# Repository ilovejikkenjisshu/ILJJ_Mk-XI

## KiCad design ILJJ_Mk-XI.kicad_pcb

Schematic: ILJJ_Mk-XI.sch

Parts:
D0: LED; LED_D5.0mm
D1, D2, D3, D4, D5, D6, D7, D8, D9, D10, D11, D12, D13, D14, D15, D16, D17, D18, D19, D20, D21, D22, D23, D24: LED; LED_Rectangular_W5.0mm_H2.0mm
J0, J1, J2, J3: Conn_02x12_Odd_Even; 5530843-1_socket
J4: Conn_02x12_Odd_Even; Pin_Header_Straight_2x12_Pitch2.54mm
J5: Conn_02x12_Odd_Even; Socket_Strip_Straight_2x12_Pitch2.54mm
R0, R1, R2, R3, R4, R5, R6, R7, R8, R9, R10, R11, R12, R13, R14, R15, R16, R17, R18, R19, R20, R21, R22, R23, R24, R25, R26, R27, R28, R29, R30, R31, R32, R33, R34, R35, R36, R37, R38, R39, R40: R; R_Axial_DIN0204_L3.6mm_D1.6mm_P2.54mm_Vertical
SW0, SW1, SW2, SW3: SW_Coded_SH-7070; Nidec_Copal_SH-7010C
U1, U2, U3: 7400; DIP-14_W7.62mm_LongPads

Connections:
/A0: J0.23, R0.1, R32.1, SW0.1
/A1: J0.21, R1.1, R31.1, SW0.2
/A2: J1.23, R2.1, R30.1, SW0.4
/A3: J1.21, R3.1, R29.1, SW0.8
/A4: J2.23, R4.1, R28.1, SW1.1
/A5: J2.21, R5.1, R27.1, SW1.2
/A6: J3.23, R6.1, R26.1, SW1.4
/A7: J3.21, R7.1, R25.1, SW1.8
/B0: J0.24, R8.1, R40.1, SW2.1
/B1: J0.22, R9.1, R39.1, SW2.2
/B2: J1.24, R10.1, R38.1, SW2.4
/B3: J1.22, R11.1, R37.1, SW2.8
/B4: J2.24, R12.1, R36.1, SW3.1
/B5: J2.22, R13.1, R35.1, SW3.2
/B6: J3.24, R14.1, R34.1, SW3.4
/B7: J3.22, R15.1, R33.1, SW3.8
/F0: J4.7, J4.8, J5.7, J5.8, U3.1, U3.2, U3.4, U3.5
/F0_1: J0.7, J0.8, J1.7, J1.8, U3.11
/F0_2: J2.7, J2.8, J3.7, J3.8, U3.8
/F1: J4.5, J4.6, J5.5, J5.6, U2.1, U2.2, U2.4, U2.5
/F1_1: J0.5, J0.6, J1.5, J1.6, U2.11
/F1_2: J2.5, J2.6, J3.5, J3.6, U2.8
/F2: J4.3, J4.4, J5.3, J5.4, U1.1, U1.2, U1.4, U1.5
/F2_1: J0.3, J0.4, J1.3, J1.4, U1.11
/F2_2: J2.3, J2.4, J3.3, J3.4, U1.8
/S0: J0.16, R24.1
/S1: J0.14, R23.1
/S2: J1.16, R22.1
/S3: J1.14, R21.1
/S4: J2.16, R20.1
/S5: J2.14, R19.1
/S6: J3.16, R18.1
/S7: J3.14, R17.1
unnamed: D0.2, R16.2
unnamed: D1.2, R17.2
unnamed: D2.2, R18.2
unnamed: D3.2, R19.2
unnamed: D4.2, R20.2
unnamed: D5.2, R21.2
unnamed: D6.2, R22.2
unnamed: D7.2, R23.2
unnamed: D8.2, R24.2
unnamed: D9.2, R25.2
unnamed: D10.2, R26.2
unnamed: D11.2, R27.2
unnamed: D12.2, R28.2
unnamed: D13.2, R29.2
unnamed: D14.2, R30.2
unnamed: D15.2, R31.2
unnamed: D16.2, R32.2
unnamed: D17.2, R33.2
unnamed: D18.2, R34.2
unnamed: D19.2, R35.2
unnamed: D20.2, R36.2
unnamed: D21.2, R37.2
unnamed: D22.2, R38.2
unnamed: D23.2, R39.2
unnamed: D24.2, R40.2
unnamed: J0.9, J4.19, J4.20
unnamed: J0.10, J1.9
unnamed: J1.10, J2.9
unnamed: J2.10, J3.9
unnamed: J3.10, J5.19, J5.20
unnamed: U1.6, U1.9, U1.10
unnamed: U1.3, U1.12, U1.13
unnamed: U2.6, U2.9, U2.10
unnamed: U2.3, U2.12, U2.13
unnamed: U3.6, U3.9, U3.10
unnamed: U3.3, U3.12, U3.13
VCC: J0.1, J0.2, J1.1, J1.2, J2.1, J2.2, J3.1, J3.2, J4.1, J4.2, J5.1, J5.2, R0.2, R1.2, R2.2, R3.2, R4.2, R5.2, R6.2, R7.2, R8.2, R9.2, R10.2, R11.2, R12.2, R13.2, R14.2, R15.2, R16.1, U1.14 (VCC), U2.14 (VCC), U3.14 (VCC)

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
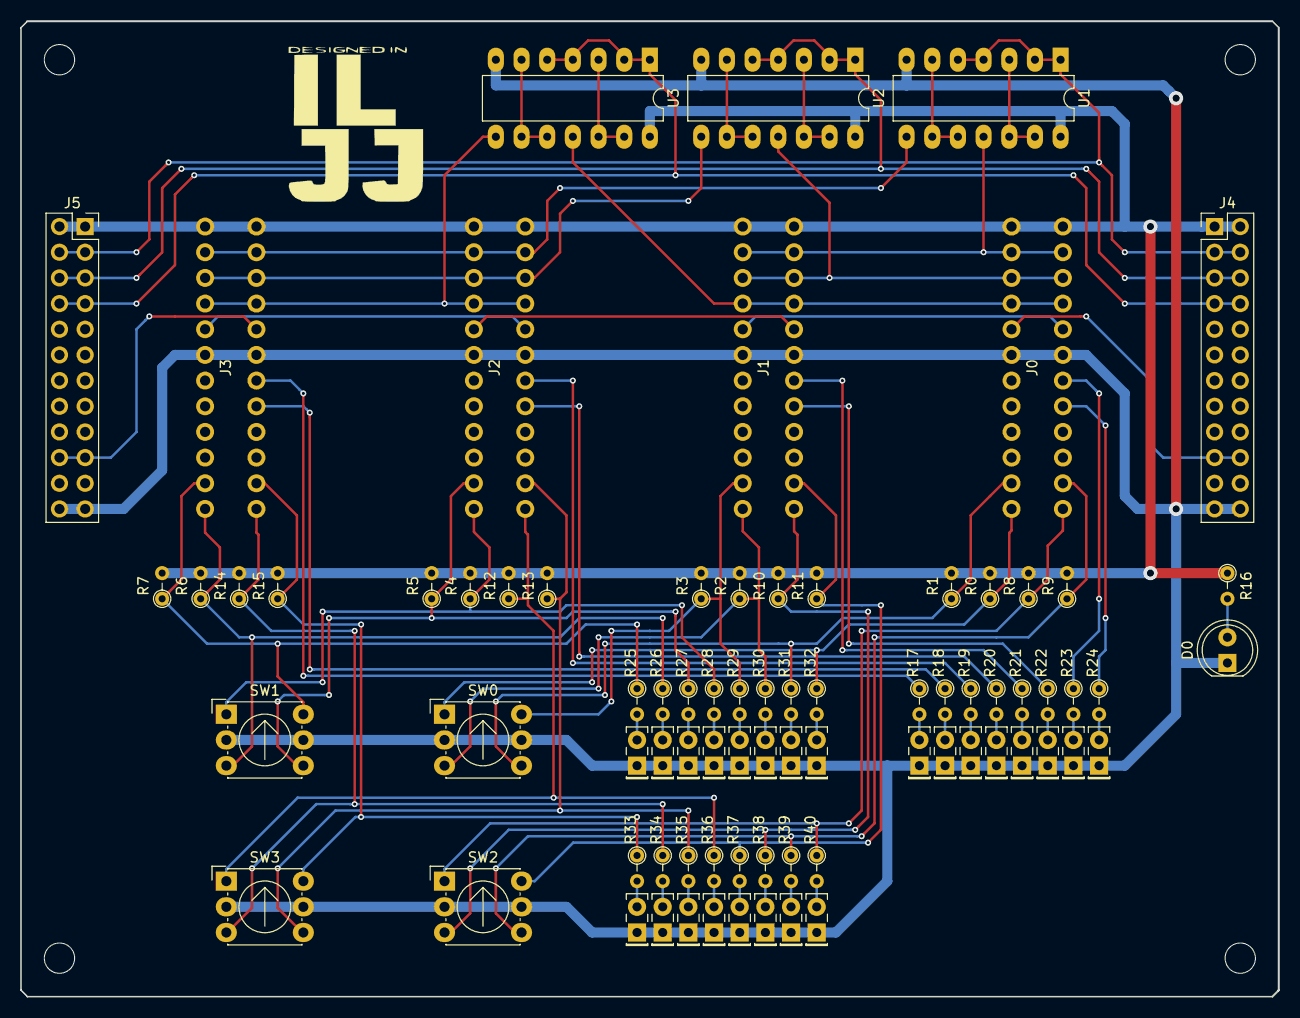
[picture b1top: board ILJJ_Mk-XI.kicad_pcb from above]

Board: 2 copper layers, 124.4 x 96.5 mm, 79 parts (0 on the bottom side), 71 nets.

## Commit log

2019-01-14 initial commit
    empty project
2019-01-15 [add] 回路図
    ひとまずはうごくと思う
2019-01-15 [add] Power indicator
2019-01-15 [add] anotation
2019-01-15 [add] some footprints
2019-01-23 [change] interface connector
2019-01-28 [add] buffer for function pin
2019-01-28 [add] footprint for card edge connector socket
2019-01-28 [add] input indicator
2019-01-29 [fix] 出力LEDが4bitしかなかった
    なんで気付かなかったんだろう...
2019-01-29 [fix] コネクタのコンポーネントを変更
2019-01-30 [add] pcb
2019-01-30 [change] バッファの配線を変更
    まあ元の配線がどう考えてもおかしい
2019-01-30 [clean] 配線のちょっとした調整
2019-01-30 [clean] アノテーション印刷の位置を調整
2019-01-30 [clean] 配線をちょっと修正
2019-01-31 [add] designed in ILJJ logo
2019-01-31 [clean] ネジ穴のリファレンスを非表示にして角を落とした
